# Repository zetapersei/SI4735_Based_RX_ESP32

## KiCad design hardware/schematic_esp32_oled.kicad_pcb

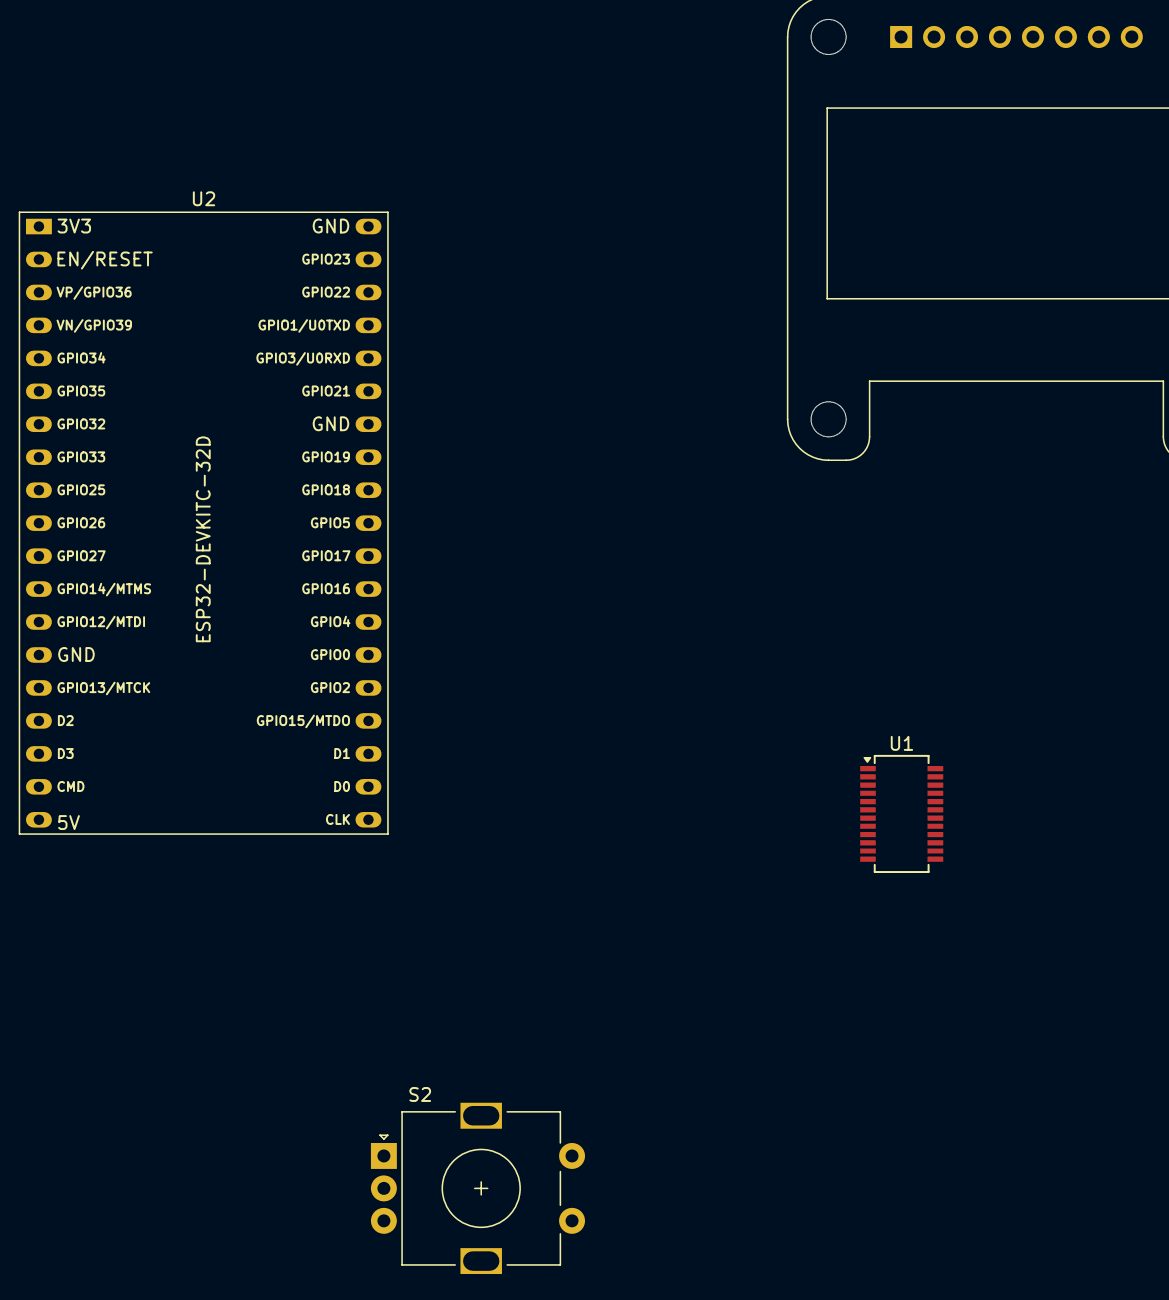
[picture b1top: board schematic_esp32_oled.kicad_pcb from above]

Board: 2 copper layers, 4 parts (0 on the bottom side), 7 nets, no tracks yet.

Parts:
S2: ENCODER-SWITCH; RotaryEncoder_Alps_EC11E-Switch_Vertical_H20mm
U1: SI4735-D60-GU; SSOP-24_3.9x8.7mm_P0.635mm
U2: ESP32-DEVKITC-32D; ESP32-DevKitC-no_ant
U$1: DISPLAY-OLED-128X64-I2C; Adafruit_SSD1306

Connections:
GND: S2.C, U1.9 (RFGND), U1.13 (GND_2), U1.14 (GND), U2.20 (GND3), U$1.1 (GND)
unnamed: U1.15 (~RST), U2.13 (IO12)
unnamed: S2.A, U2.15 (IO13)
unnamed: S2.B, U2.12 (IO14)
unnamed: U1.17 (SCLK), U2.22 (IO22), U$1.3 (SCL)
unnamed: U1.18 (SDIO), U2.25 (IO21), U$1.4 (SDA)
VCC: U1.20 (VD), U1.21 (VA), U2.1 (3V3), U$1.2 (VCC)

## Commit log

2025-01-22 new file: .gitignore new file: .vscode/extensions.json new file: include/README new file: lib/README new file: platformio.ini new file: src/main.cpp new file: test/README
2025-01-22 modified: platformio.ini new file: src/DSEG7_Classic_Regular_16.h new file: src/OLED_ALL_IN_ONE.ino new file: src/Rotary.cpp new file: src/Rotary.h deleted: src/main.cpp
2025-01-22 new file: hardware/schematic_esp32_oled_all_in_one.png
2025-01-23 new file: hardware/fp-info-cache new file: hardware/schematic_esp32_oled-backups/schematic_esp32_oled-2025-01-22_200021.zip new file: hardware/schematic_esp32_oled-backups/schematic_esp32_oled-2025-0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
2025-01-23 new file: hardware/Datasheet/Si4730-31-34-35-D60.pdf new file: hardware/schematic_esp32_oled-backups/schematic_esp32_oled-2025-01-23_103532.zip modified: hardware/schematic_esp32_oled.kicad_sch
